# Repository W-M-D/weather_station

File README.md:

# weather_station

The ultimate in nrf52832 based APRS weather stations! 

Just a quick update after finding that you can buy a weather station replacement kit for ~$70 that has a few radios that is already supported by rtl_433 i sat down and did some thinking. What could i do that would be more universal. Like the ultimate Ham hacking kit. After much debate with myself. I have decided to make something much more generic.  But i also wanted to create something that was much more than a simple dev board. I'm keeping the universality down to one radio besides the Bluetooth one. But i am going to add a raspberry pi header for reasons. My goal is to make a device that, with your ham radio, you can create anything you desire within the limits of the community and APRS.

Another update i'm still going to make a version of the board with out the raspberry pi HAT. I'm going to elimiate most of the hardware since i'm planning on reading from external sensors. I'm planning on breaking out the nrf52832 to pin headers to connect the hardware. This will still run off 4 18650s and will still have the solar MPPT circuit.

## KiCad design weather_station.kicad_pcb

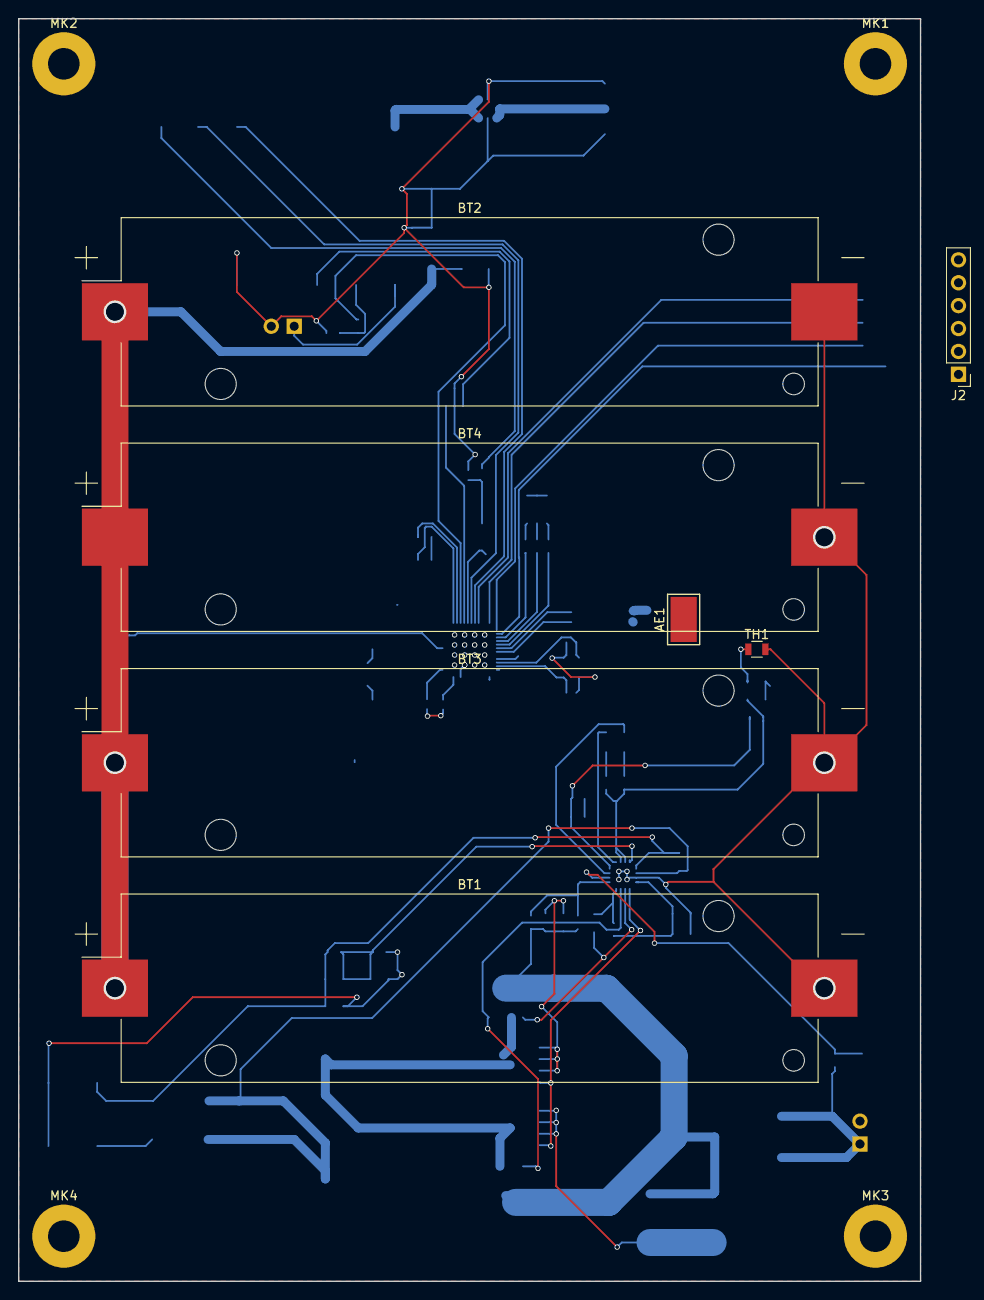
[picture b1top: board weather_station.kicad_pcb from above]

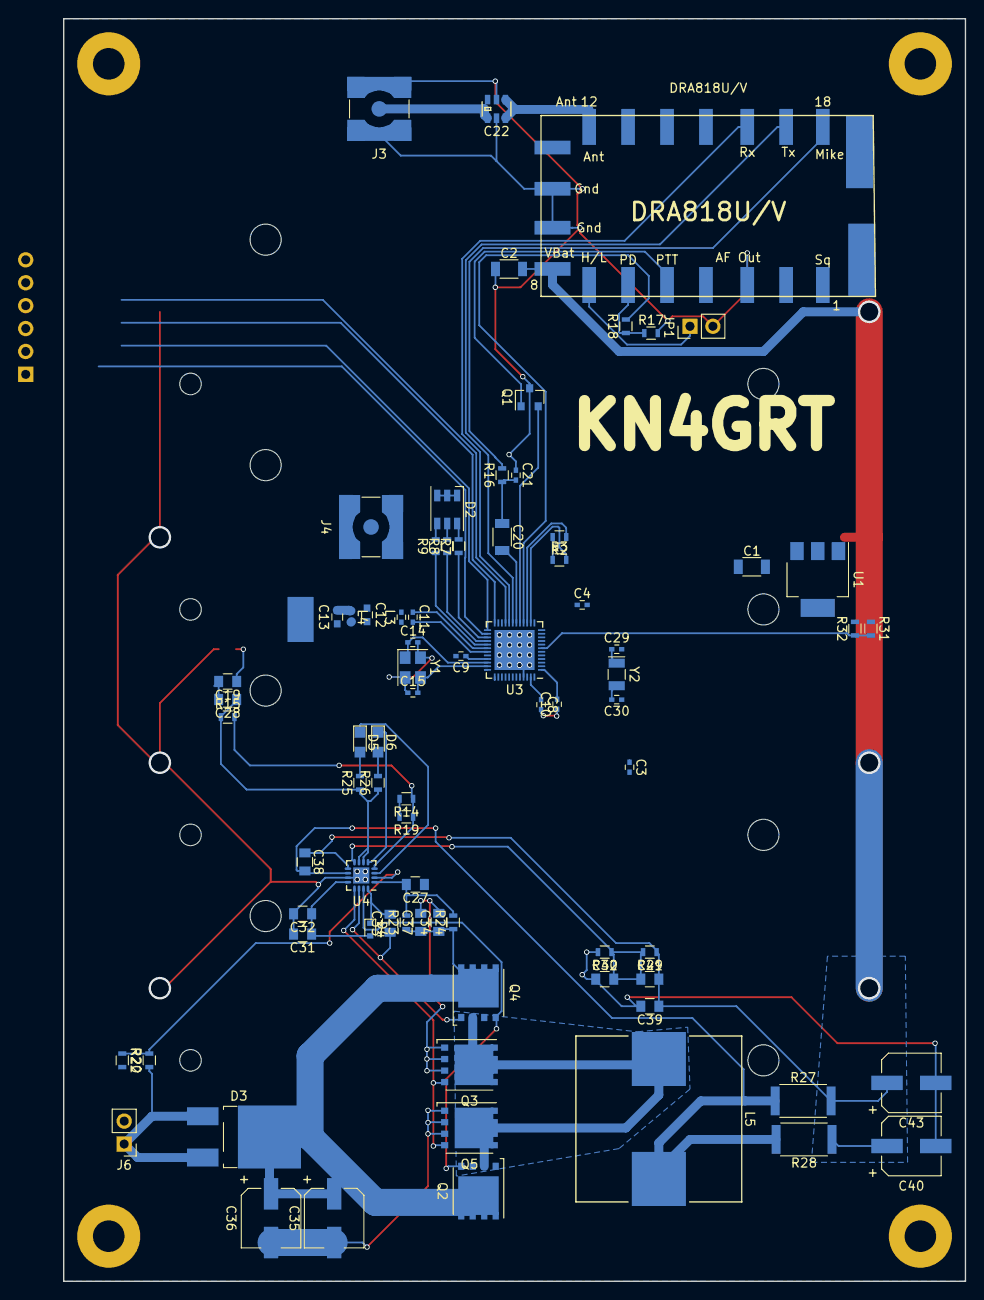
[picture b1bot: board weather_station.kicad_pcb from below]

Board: 2 copper layers, 100.0 x 140.0 mm, 90 parts (79 on the bottom side), 52 nets.

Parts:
AE1: ant; SMA
BT1, BT2, BT3, BT4: 18650Cell; Keystone_1042_1x18650
C1, C2, C20: 10uF; C_1206
C3: 4.7uF; C_0402
C4, C10, C11, C21: 100nF; C_0402
C8: 1uF; C_0402
C9: 100pF; C_0402
C12, C13: tuning_cap; C_0603
C14, C15: 12pF; C_0402
C19: -; C_0805
C22: EMI_Filter_C; FV1206-1
C27, C28, C32, C34, C37, C39: 1.0uF; C_0805
C29, C30: C_Small; C_0402
C31, C33, C38, C41, C42: 0.1uF; C_0805
C35, C43: 100uF; CP_Elec_6.3x7.7
C36, C40: 47uF; CP_Elec_6.3x7.7
D2: LTRB GFSF; LED_RGB_PLCC-6
D3: MBRD10100CT; TO-252-2_Rectifier
D4: D_Schottky; D_SOD-523
D5, D6: LED; LED_0805
DRA1: DRA818U
J2: Conn_01x06; Pin_Header_Straight_1x06_Pitch2.54mm
J3, J4: Conn_Coaxial; SMA_SMD_Jack_Straight
J6: SOLAR; Pin_Header_Straight_1x02_Pitch2.54mm
JP1: Jumper; Pin_Header_Straight_1x02_Pitch2.54mm
L3: 3.3nH; C_0402
L4: tuning_inductor; C_0402_NoSilk
L5: 3.3uH; Inductor_Wurth_HCI-1890
MK1, MK2, MK3, MK4: Mounting_Hole; MountingHole_3.5mm_Pad
Q1: Q_NMOS_DGS; SOT-23
Q2, Q3, Q4, Q5: FDMS8050; TDSON-8-1
R2, R3: 1.8kΩ; R_0603
R7, R8, R9: 255Ω; R_0603
R14: 10kΩ; R_0603
R15, R25, R26: 5.23kΩ; R_0603
R16, R30, R31, R32: 100kΩ; R_0603
R17: 3.3kΩ; R_0603
R18: 1.8KΩ; R_0603
R19: 30.1kΩ; R_0603
R20, R29: 499kΩ; R_0603
R22: 36kΩ; R_0603
R23: -; R_0603
R24: 10Ω; R_0603
R27, R28: 0.010Ω; R_2512
TH1: Thermistor_NTC; R_0805
U1: LT1129-3.3_SOT223; SOT-223-3Lead_TabPin2
U3: nRF52832; UQFN-48-1EP_6x6mm_Pitch0.4mm
U4: BQ24650; QFN-16-1EP_3x3mm_Pitch0.5mm
Y1: FL3200037; Crystal_SMD_3225-4pin_3.2x2.5mm
Y2: 32.786khz; Crystal_SMD_EuroQuartz_EQ161-2pin_3.2x1.5mm

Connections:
+3V3: C1.2, C3.2, C4.2, J2.1, R2.2, R3.1, U1.3, U3.13, U3.36, U3.48
+BATT: BT1.1, BT2.1, BT3.1, BT4.1, C2.2, C38.1, C39.1, C40.1, C41.2, C43.1, DRA1.8, R27.2, R28.1, R29.1, R31.1, U1.1, U4.9
/power/HIGH_DRIVE: Q2.4, Q4.4, U4.15
/power/LOW_DRIVE: Q3.4, Q5.4, U4.13
/power/MPPTSET: R20.2, R22.1, U4.2
/power/STAT1: D5.1, U4.3
/power/STAT2: D6.1, U4.5
/power/VREF: C28.1, R15.1, R25.1, R26.1, U4.6, U4.7
B_LED: R9.1, U3.29
GND: BT1.2, BT2.2, BT3.2, BT4.2, C1.1, C2.1, C3.1, C4.1, C8.2, C9.2, C10.1, C12.1, C13.1, C14.2, C15.1, C19.2, C21.1, C22.2, C27.1, C28.2, C29.2, C30.1, C31.2, C32.2, C34.2, C35.2, C36.2, C37.2, C39.2, C40.2, C42.1, C43.2, D2.1, D2.2, D2.3, DRA1.1, DRA1.3, DRA1.9, DRA1.10, J2.6, J3.2, J4.2, J6.2, JP1.2, Q1.3, Q3.1, Q3.2, Q3.3, Q5.1, Q5.2, Q5.3, R14.2, R17.2, R19.2, R22.2, R30.2, R32.2, TH1.2, U1.2, U3.45, U3.49, U4.11, U4.17, Y1.2, Y1.4
G_LED: R8.1, U3.28
unnamed: AE1.1, C13.2, L4.1
unnamed: C8.1, U3.47
unnamed: C9.1, U3.33
unnamed: C10.2, U3.1
unnamed: C11.1, L3.2, U3.30
unnamed: C11.2, U3.31
unnamed: C12.2, J4.1, L3.1, L4.2
unnamed: C19.1, R14.1, R15.2, R19.1, TH1.1, U4.4
unnamed: C20.1, C21.2, R16.1
unnamed: C22.1, J3.1
unnamed: C22.3, DRA1.12
unnamed: C27.2, R23.2, R24.2, U4.1
unnamed: C31.1, C32.1, D4.2, U4.12
unnamed: C33.1, L5.1, Q2.1, Q2.2, Q2.3, Q3.5, Q4.1, Q4.2, Q4.3, Q5.5, U4.14
unnamed: C33.2, D4.1, U4.16
unnamed: C34.1, C35.1, C36.1, C37.1, D3.2, Q2.5, Q4.5, R23.1, R24.1
unnamed: C38.2, L5.2, R27.1, R28.2, U4.10
unnamed: C41.1, C42.2, R29.2, R30.1, U4.8
unnamed: D2.4, R9.2
unnamed: D2.5, R8.2
unnamed: D2.6, R7.2
unnamed: D3.1, D3.3, J6.1, R20.1
unnamed: D5.2, R25.2
unnamed: D6.2, R26.2
unnamed: DRA1.5, Q1.1
unnamed: DRA1.6, R17.1, R18.1
unnamed: DRA1.7, JP1.1
unnamed: DRA1.18, R16.2
RADIO_DATA: C20.2, U3.18
RADIO_PD: R18.2, U3.16
RADIO_PTT: Q1.2, U3.17
RADIO_UART_RX: DRA1.16, U3.20
RADIO_UART_TX: DRA1.17, U3.19
R_LED: R7.1, U3.27
SCL: R2.1, U3.15
SDA: R3.2, U3.14
XC1: C14.1, U3.34, Y1.1
XC2: C15.2, U3.35, Y1.3
XL1: C30.2, U3.2, Y2.2
XL2: C29.1, U3.3, Y2.1
v_batt: R31.2, R32.1, U3.7

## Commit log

2018-02-04 init add
2018-02-04 basing solar power supply off of openMPPT
2018-02-04 well this is going to be easy to route...
2018-02-04 almost done
2018-02-04 well that wasn't centered
2018-02-04 might as well be able to monitor battery voltage from the nrf52832
2018-02-05 i think that's enough for now
2018-02-12 some cost savings
2018-04-03 Adding antennas
2018-04-03 some changes
